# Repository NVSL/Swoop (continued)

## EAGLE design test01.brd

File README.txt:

Swoop is a library of Python objects for representing and manipulating
Cadsoft Eagle board, schematic, and library files used in designing printed
circuit boards (PCBs).  It parses an input Eagle file, creates a internal
representation data structure that represents the file's contents,
provides accessors and mutators to query, read, and modify those contents, and
generates valid Eagle files as output.

Swoop was created by the NVSL (http://nvsl.ucsd.edu/) UCSD
(http://www.ucsd.edu/) as part of the Gadgetron project
(http://nvsl.ucsd.edu/index.php?path=projects/gadget)

Documentation is available here: http://nvsl.ucsd.edu/Swoop

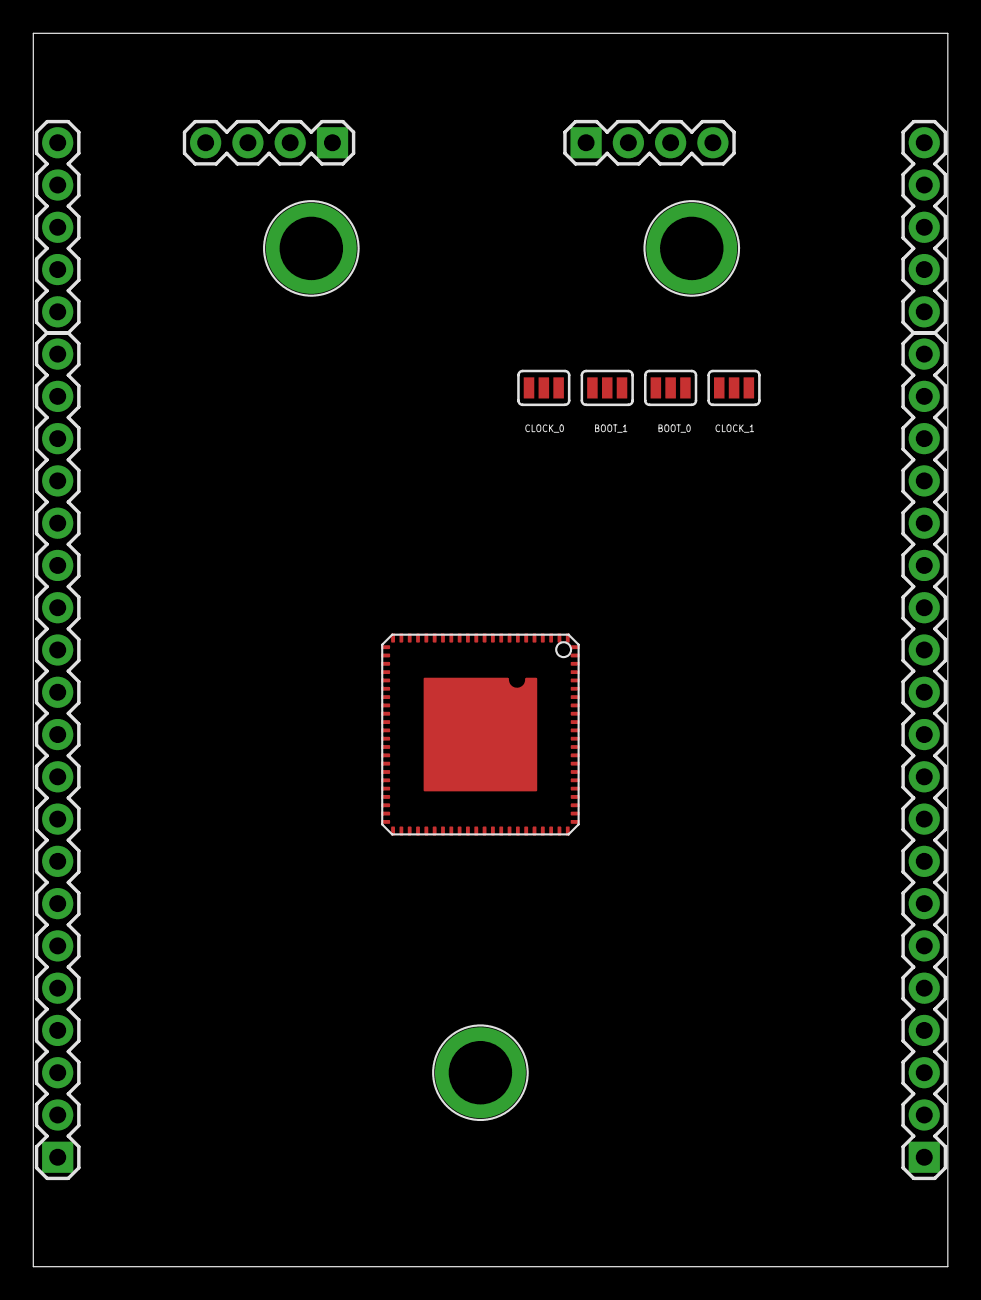
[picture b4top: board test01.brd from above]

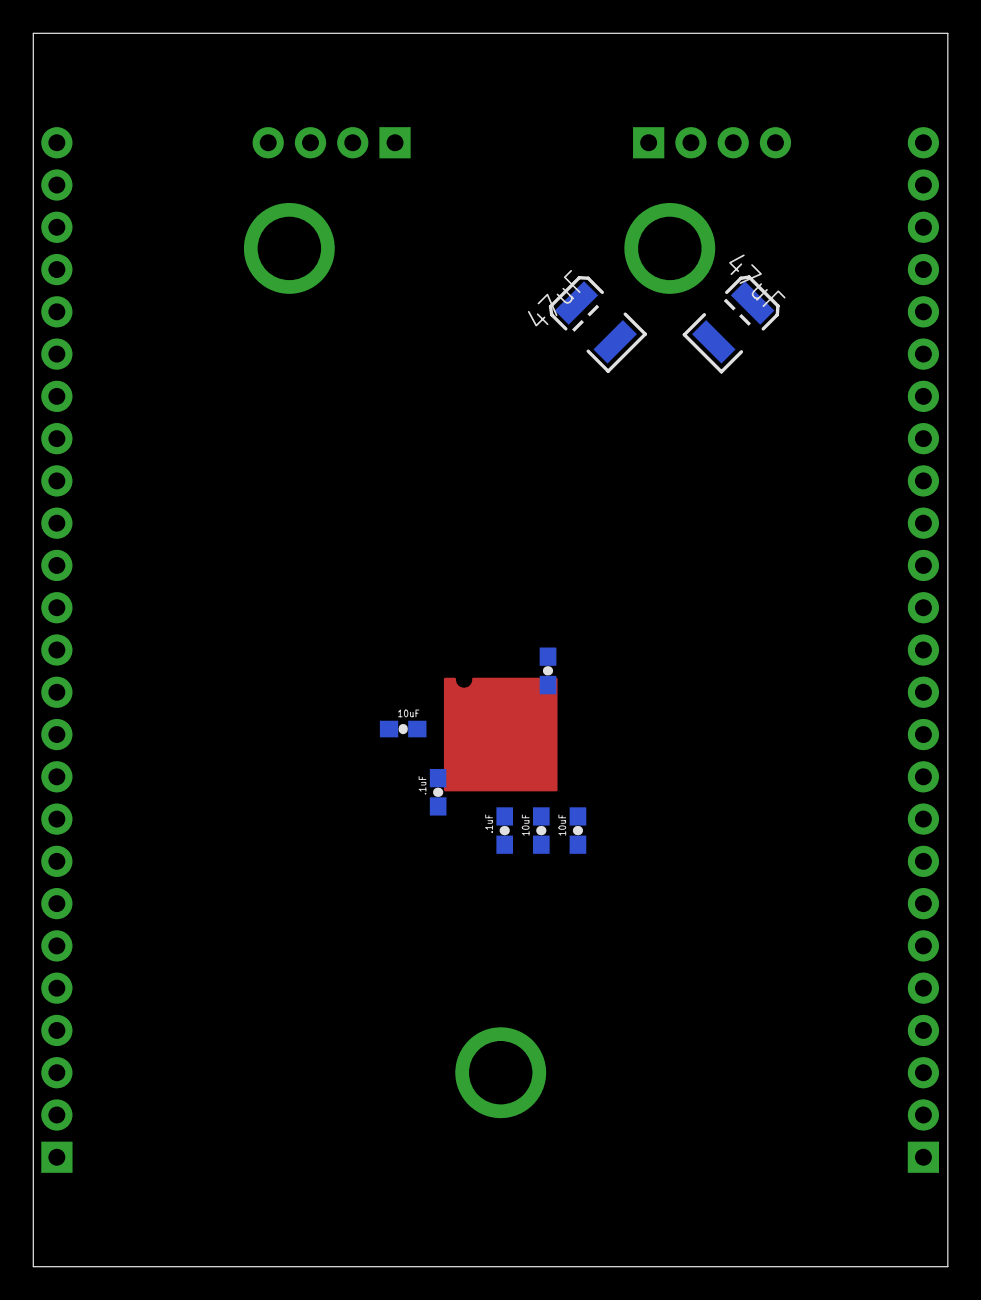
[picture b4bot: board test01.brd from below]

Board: 2 copper layers, 55.0 x 74.1 mm, 22 parts (8 on the bottom side), 57 nets, no tracks yet.

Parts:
1.25V, 3.3V: BANANA_CONN
BOOT_0, BOOT_1: SJ_3
C1, C2, C5: 10uF; 0603-CAP
C3, C4, C6: .1uF; 0603-CAP
C7, C8: 47uF; EIA3528
CLOCK_0: SJ_3
CLOCK_1: aoeu; SJ_3
J3: BANANA_CONN
JP2, JP4: M20; 1X20
JP3, JP7: 1X05
JP5, JP6: 1X04
U$1: ADSP-21479; QFN-88

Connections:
BOOT_CFG0: BOOT_0.2, U$1.2
BOOT_CFG1: BOOT_1.2, U$1.5
CLKIN: JP3.5, U$1.9
CLK_CFG0: CLOCK_0.2, U$1.7
CLK_CFG1: CLOCK_1.2, U$1.1
DAI_P01: JP2.9, U$1.37
DAI_P02: JP2.8, U$1.38
DAI_P03: JP2.13, U$1.31
DAI_P04: JP2.1, U$1.51
DAI_P05: JP2.6, U$1.43
DAI_P06: JP2.7, U$1.42
DAI_P07: JP2.11, U$1.35
DAI_P08: JP2.2, U$1.50
DAI_P09: JP2.5, U$1.44
DAI_P10: JP2.4, U$1.45
DAI_P11: JP4.7, U$1.58
DAI_P12: JP4.6, U$1.57
DAI_P13: JP2.12, U$1.34
DAI_P14: JP4.1, U$1.52
DAI_P15: JP4.5, U$1.56
DAI_P16: JP4.4, U$1.55
DAI_P17: JP4.3, U$1.54
DAI_P18: JP4.2, U$1.53
DAI_P19: JP2.10, U$1.36
DAI_P20: JP2.3, U$1.48
DPI_P01: JP3.2, U$1.16
DPI_P02: JP3.1, U$1.17
DPI_P03: JP7.5, U$1.18
DPI_P04: JP7.3, U$1.21
DPI_P05: JP7.4, U$1.20
DPI_P06: JP7.2, U$1.22
DPI_P07: JP2.20, U$1.25
DPI_P08: JP7.1, U$1.24
DPI_P09: JP2.19, U$1.26
DPI_P10: JP2.18, U$1.27
DPI_P11: JP2.17, U$1.28
DPI_P12: JP2.16, U$1.29
DPI_P13: JP2.15, U$1.30
DPI_P14: JP2.14, U$1.32
FLAG0: JP4.10, U$1.68
FLAG1: JP4.11, U$1.70
FLAG2: JP4.12, U$1.71
FLAG3: JP4.13, U$1.72
GND: BOOT_0.1, BOOT_1.1, C1.1, C2.1, C3.1, C4.1, C5.1, C6.1, C7.C, C8.C, CLOCK_0.1, CLOCK_1.1, J3.P$1, U$1.6, U$1.60, U$1.73, U$1.74, U$1.76, U$1.PAD
TCK: JP4.18, U$1.84
TDI: JP4.17, U$1.83
TDO: JP4.16, U$1.80
THD_B51AD: JP4.9, U$1.62
THD_M: JP4.8, U$1.61
TMS: JP4.20, U$1.87
VDD_EXT+THD: 3.3V.P$1, BOOT_0.3, BOOT_1.3, C1.2, C2.2, C3.2, C4.2, C7.A, CLOCK_0.3, CLOCK_1.3, JP5.1, JP5.2, JP5.3, JP5.4, U$1.3, U$1.11, U$1.23, U$1.40, U$1.47, U$1.63, U$1.75, U$1.81
VDD_INT: 1.25V.P$1, C5.2, C6.2, C8.A, JP6.1, JP6.2, JP6.3, JP6.4, U$1.4, U$1.8, U$1.12, U$1.13, U$1.15, U$1.19, U$1.33, U$1.39, U$1.41, U$1.46, U$1.49, U$1.59, U$1.64, U$1.65, U$1.66, U$1.67, U$1.69, U$1.77, U$1.82, U$1.85, U$1.88
XTAL: JP3.4, U$1.10
~EMU: JP4.15, U$1.79
~RESET: JP4.19, U$1.86
~RESETOUT/~RUNRSTIN: JP3.3, U$1.14
~TRST: JP4.14, U$1.78

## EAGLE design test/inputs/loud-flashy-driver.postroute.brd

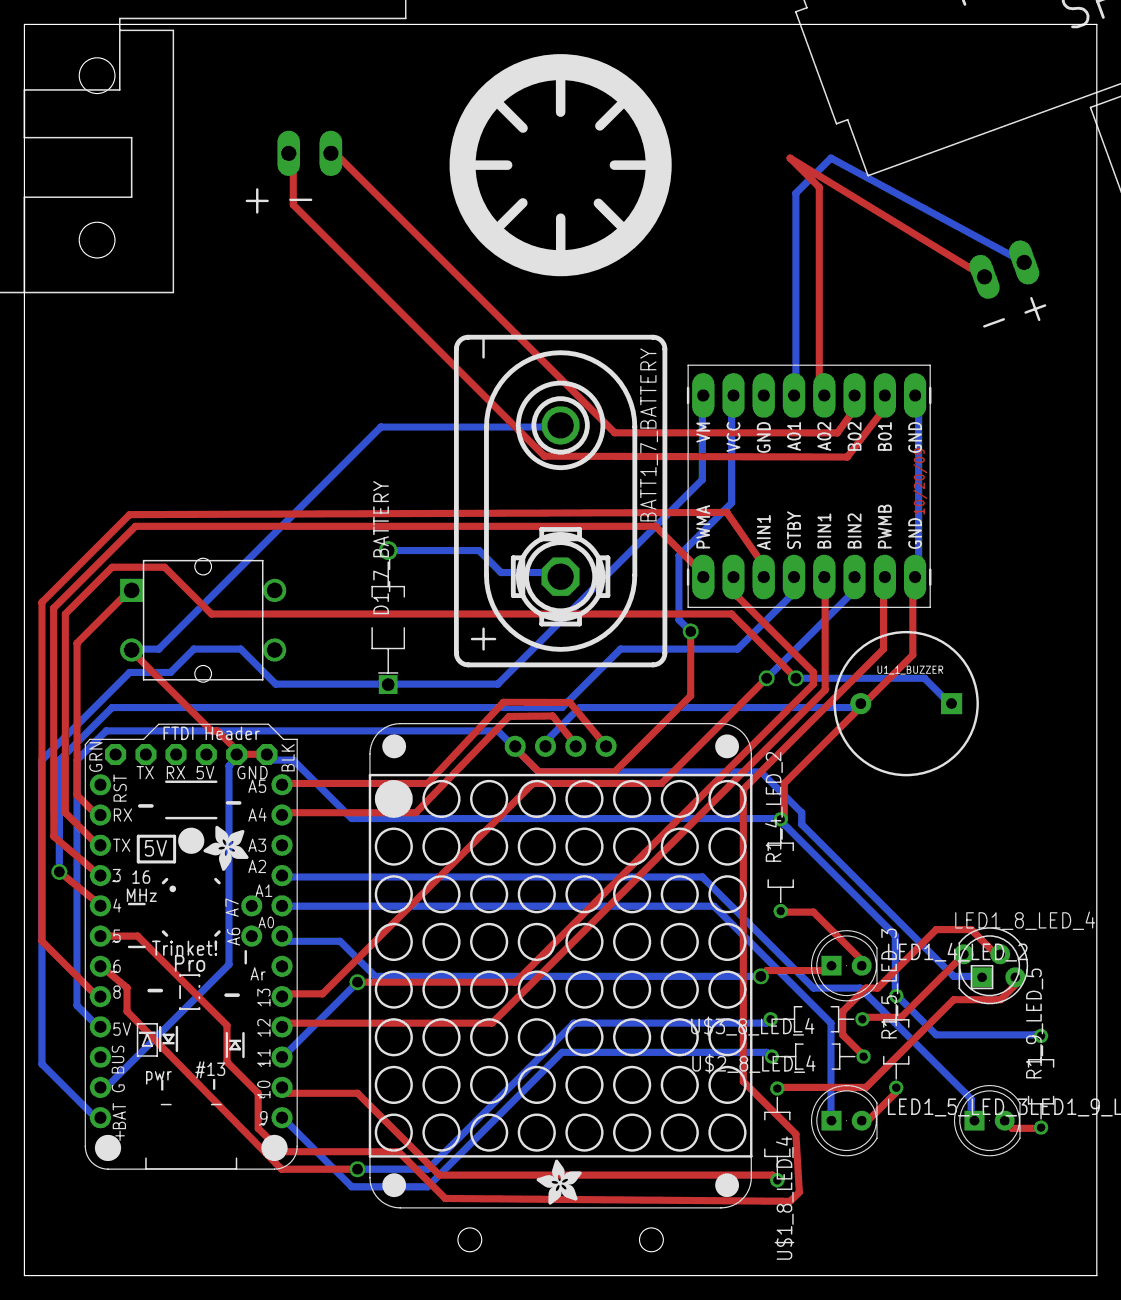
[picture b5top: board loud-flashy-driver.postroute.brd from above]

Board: 2 copper layers, 90.0 x 105.0 mm, 21 parts (0 on the bottom side), 31 nets.

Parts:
B1_0_BUTTON: BUTTON-TACTILE-SQUARE; BUTTON-TACTILE-SQUARE-ADAFRUIT1010
BATT1_7_BATTERY: BATTERY-9V-VERTICAL; BATTERY_9V_KEYSTONE_968
D1_7_BATTERY: DIOAD1125W78L520D270_HS
DRVR_2_DRIVE: SPARKFUN_DUAL_MOTOR_DRIVER-BOB; SPARKFUN_DUAL_MOTOR_DRIVER
LED1_4_LED_2, LED1_5_LED_3, LED1_9_LED_5: LED5MM
LED1_8_LED_4: RGBLED_CA-5MM; LED5MMRGB
L_2_DRIVE: SOLARBOTICS_GM2_LEFTSPARKFUN_HOBBY; SPARKFUN_HOBBY_MOTOR_LEFT
R1_4_LED_2, R1_5_LED_3, R1_9_LED_5: 330; RESAD770W45L370D210_HS
R_2_DRIVE: SOLARBOTICS_GM2SPARKFUN_HOBBY; SPARKFUN_HOBBY_MOTOR
U1_1_BUZZER: BUZZER-12MM
U1_3_DISPLAY_2: ADAFRUIT-1.2IN-8X8-LED-BACKPACK
U1_6_CASTER: ADAFRUIT-3/4IN-CASTER
U1_10_BRAIN: ADAFRUIT-PRO-TRINKET-5V
U1_11_PENHOLDER: PENHOLDER
U$1_8_LED_4, U$2_8_LED_4: 100; RESAD770W45L370D210_HS
U$3_8_LED_4: 150; RESAD770W45L370D210_HS

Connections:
+5V_10_BRAIN: DRVR_2_DRIVE.VCC, LED1_8_LED_4.2, U1_3_DISPLAY_2.VDD, U1_10_BRAIN.+5V
A0_10_BRAIN: LED1_4_LED_2.A, U1_10_BRAIN.A0
A01_2_DRIVE: DRVR_2_DRIVE.A01, R_2_DRIVE.+
A1_10_BRAIN: LED1_5_LED_3.A, U1_10_BRAIN.A1
A02_2_DRIVE: DRVR_2_DRIVE.A02, R_2_DRIVE.-
A2_10_BRAIN: LED1_9_LED_5.A, U1_10_BRAIN.A2
A4_10_BRAIN: U1_3_DISPLAY_2.SDA, U1_10_BRAIN.A4
A5_10_BRAIN: U1_3_DISPLAY_2.SCL, U1_10_BRAIN.A5
B01_2_DRIVE: DRVR_2_DRIVE.B01, L_2_DRIVE.+
B02_2_DRIVE: DRVR_2_DRIVE.B02, L_2_DRIVE.-
D3_10_BRAIN: DRVR_2_DRIVE.PWMA, U1_10_BRAIN.D3
D4_10_BRAIN: DRVR_2_DRIVE.STBY, U1_10_BRAIN.D4
D5_10_BRAIN: DRVR_2_DRIVE.PWMB, U1_10_BRAIN.D5
D6_10_BRAIN: U1_10_BRAIN.D6, U$3_8_LED_4.2
D8_10_BRAIN: DRVR_2_DRIVE.AIN1, U1_10_BRAIN.D8
D9_10_BRAIN: U1_10_BRAIN.D9, U$2_8_LED_4.2
D10_10_BRAIN: U1_10_BRAIN.D10, U$1_8_LED_4.2
D11_10_BRAIN: DRVR_2_DRIVE.AIN2, U1_10_BRAIN.D11
D12_10_BRAIN: DRVR_2_DRIVE.BIN1, U1_10_BRAIN.D12
D13_10_BRAIN: DRVR_2_DRIVE.BIN2, U1_10_BRAIN.D13
GND_0_BUTTON: B1_0_BUTTON.S, BATT1_7_BATTERY.N, DRVR_2_DRIVE.GND, DRVR_2_DRIVE.GND2, R1_4_LED_2.2, R1_5_LED_3.2, R1_9_LED_5.2, U1_1_BUZZER.-, U1_3_DISPLAY_2.GND, U1_10_BRAIN.GND, U1_10_BRAIN.GND1, U1_10_BRAIN.GND2
unnamed: LED1_4_LED_2.K, R1_4_LED_2.1
unnamed: LED1_5_LED_3.K, R1_5_LED_3.1
unnamed: BATT1_7_BATTERY.P, D1_7_BATTERY.A
unnamed: LED1_8_LED_4.4, U$1_8_LED_4.1
unnamed: LED1_9_LED_5.K, R1_9_LED_5.1
unnamed: LED1_8_LED_4.3, U$2_8_LED_4.1
unnamed: LED1_8_LED_4.1, U$3_8_LED_4.1
RXD1_10_BRAIN: B1_0_BUTTON.P, U1_10_BRAIN.RXD1
TXD1_10_BRAIN: U1_1_BUZZER.+, U1_10_BRAIN.TXD1
VM_2_DRIVE: D1_7_BATTERY.C, DRVR_2_DRIVE.VM, U1_10_BRAIN.VBAT

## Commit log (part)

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2014-11-14 Example of circuits from code
2014-11-14 Framework for circuits from code
2014-11-17 Tester for HighEagle interface
2014-11-19 More circuits by code import implementation
2014-11-23 one more feature
2015-01-06 bug fixes for labels/segments
2015-01-21 reorged part resolution code
2015-01-22 Added .api.gspec
2015-01-24 Fixed some bugs in part resolution and improved error handling for parsing Digikey spreadsheets
2015-01-25 test for unit parsing
2015-01-28 missing code
2015-02-03 Fixed and re-enabled a test
2015-02-05 test fixes
2015-02-09 Better part parameter parsing
    Fixed curvature of wires
    Support for diodes
    Multiple part database support
    Standardized attributes
    fixed tests
    code for building GENERIC, RESOLVED, and UNRESOLVED devicesets automatically
2015-02-10 Resonator support. Better tests and Makefiles
2015-02-12 Cleanup, error checking, and pretty printing of values in resolved parts
2015-02-12 Get rid of nF
2015-02-16 Repair base.lbr
2015-02-18 Added EagleTools.py for useful functions that don't belong in HighEagle.py. Current tools are for cleaning up layers in eagle files.
    Added EagleFilePartVisitor base class for building visitors.
    Made sure layers are in sorted order.
    Updated NVSLLayers.lbr to match Eagle manual + gadgetron layers
    Picker.py now fixes up layers automatically.
    Picker.py now takes resolver library and layers library
    Cleaner tests
2015-02-22 Part picker cleanup.
    Added environment variable support to GadgetronConfig
    Made picker use GadgetronConfig
    Added picker configuration variables to gadgetron config
    Move picker libraries into Libraries/ hierarchy.
    Moved standard layer lib into Libraries/Parts/Eagle
    Added CircuitsByCode to PATH in setup.
2015-02-23 Moved picker tool to its directory. Renamed koala
2015-02-24 Added support for new leaf tags that appear in brd files.
    Started using logging module for logging. We should use it more: import logging as log
    New command line options for Koloa to make it easier to diagnose unresolved components. You can specify parts to resolve and ask for verbose mode.
    Added a kludge to work around problems rendering some values when printing out resolved parts in Koala
    New --force option for fixEagle to forcibly install layers.
2015-03-01 Complete rework of HighEagle.py.
    Instead of being written by hand, it's autogenerated from HighEagle.jinja.py.
    A couple of tools, most notably GenerateHigHeagle.py use Jinja and the
    eagle DTD to autogenerate classes for eagle files.
    Look at GenerateHigHeagle.py for comments describing how it works.
    This change adds some complexity. GenerateHighEagle.py is not so easy
    to edit and you need to know the basics of the jinja templating
2015-03-01 bug fixes
2015-03-02 Documentation. See the top of GenerateHighEagle.py
2015-03-02 Small bug fix for _EXTERNAL_ devices
2015-03-03 Lots of documentation. Code cleanup. Got rid perl-generated intermeidate attribute file. Fix for lists of attributes in <element>. Some test boards and schematics.
2015-03-03 Better type information for parsing and documentation.
2015-03-05 Removed arguments from all constructors to make extending classes easier.
2015-03-05 Typeo
2015-03-08 The libraries are in place for Koala, thanks mostly to Stephen Deiss.
    Generating the CSV file for the parts database is very error-prone.
2015-03-09 Added koala to the gadget making tool chain.
    Update 3mm, 5mm, and 10mm LEDs to use koala for their resistors. It's a start.
    Fix to make jettest build again.
    modified gadgetmaker2 to use HighEagle for file output (and to normalize the layers on the .brd and .sch files it generates)
    Docs for EagleTools.py
    Added function to EagleTools.py to propagate parts from .sch to .brd files.
    Added function to EagleTools.py rebuild signals in brd based on sch.
2015-03-11 missing file
2015-03-11 Doc cleanup for name change
2015-03-12 asciitree for library generation. Moved tests for Koala and Swoop to python unittest.
2015-03-14 build fixes
2015-03-14 Made the Swoop interface slightly more fluent by changing filter_* to with_*
2015-03-17 A probably-to-complex mechanism for extending Swoop.
2015-04-03 buildPackageSVGs should center the artwork inside the SVG bounding box.
2015-04-06 Accounting for polygon and wire widths in get_bounding_rectangle.
2015-04-08 Swoop extensions folder
2015-04-09 made 'width' on <dimension> tags optional because eagle omit it sometimes
2015-04-15 Improved bounding boxes, with tests. Doesn’t work with all types of pads yet. Also supports querying board elements now
2015-04-17 Major improvements to bounding boxes. Now supports: arcs (with width), long pads, offset pads, rotated offset/long pads, rotated octagons. With tests.
2015-04-27 Monkey patch chaos: experimented with just normal monkey patching instead of Mixin and repeatedly doing isinstance(). Not sure which is worse.
2015-05-01 Example for on-top-of-Swoop layer use
2015-05-04 Tying up loose ends in Swoop. Clean up docs.
2015-05-04 disable tests if we don't have Rectangle
2015-05-04 bug fix"
2015-05-05 More work towards distribution
2015-05-05 reorg for distribution
2015-05-06 yet still more prep for distribution
2015-05-08 Complete reorganization to match setuptool standard practice.
    Setuptools is really pretty awesome. Especially 'develop' mode
    Also, if you
    export USE_VENV=yes
    Everything gadgetron related will get its own python directory (in Gadgets/Python/). This will also let you use develop mode.
2015-05-08 Significantly cleaned up the monkey patch chaos. Rather than use isinstance() or monkey patching, I tried to take advantage of duck typing and hasattr().
    Mirroring each individual child element of a package in SwoopGeom should now look exactly the same as if you mirrored the whole package in Eagle.
2015-05-08 Bad indexing
2015-05-08 doc fixes
2015-05-15 -RGBLED had a bunch of stuff missing from the important layers -Did a library update on SF-dual-motor-driver because its package was wrong (I’m not using its package anyway but why not)
2015-05-15 Package bounding box
2015-05-30 Unused argument
2015-06-13 Panelize script
2015-06-17 broke out basic eagle code processor schematics into seperate class
2015-06-18 new quadcopter schematic
    Some type checking on arguments to Swoop functions.
    Swoop tool to snap schematic items to a grid
    Swoop documentation fixes.
    New Dual Motor component.
    Some more cap sizes.
    Koala bug fixes.
2015-06-29 better support for instances
2015-07-15 More gracefully handle missing layers
2015-07-16 tricky bug fix
2015-07-22 bug fix for singleton parent
2015-07-23 More comments
2015-07-26 use getters consistently
2015-07-27 Improved consistency for get_layers(). Added type checking for attribute setters. got rid of Attribute.in_library. Added support for dumping XML version of an EFP. Tests for Attribute.constant handli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
2015-08-03 Test for Swoop not opending Quadcopter.koala.sch
2015-08-04 Swoop opening and writing Trinket will cause bug, test added
2015-08-07 error handling
2015-09-13 Circular rubouts work
2015-09-24 Convert Eagle wire paths into laser turtle code.
2015-10-11 No CGAL unless we need it
2015-10-11 Add back in skipping tests
2015-10-13 Wrote test for overlap checking, fixed things
2015-10-14 It did not like that import
2015-10-28 Forgot file
2015-11-09 irrelevant change
2015-11-19 Add support for Eagle 7.4 and 7.5
2015-12-23 Use CGAL segments for wires with width == 0 as well wires without a width
2015-12-24 Support for module-based mixins
2015-12-26 Improved layer lookup and layer mirroring
2015-12-27 First parts of a Shapely-based geometry extension. It's cleaner than the CGAL-based one system. Still much to do.
2015-12-31 Renamed Shapely to ShapelySwoop
2015-12-31 Improved tests
2015-12-31 Tool renumber layers
2015-12-31 renumbered layers
2016-01-07 Produce smaller svgs
2016-02-17 Support for parsing DRU files
2016-02-18 Docs for DRU file in open((
2016-02-20 .gitignore
2016-02-24 Nicer errors when parsing problems occur
2016-02-25 Mirroring fixes
2016-02-28 Don't open the file until writing it assured
2016-03-02 Better parsing error reporting. Move element transforms to static methods. New and improved utilities for board building
2016-03-08 handle curves properly
2016-03-08 add library cache to docs
2016-03-09 Support for text.
2016-03-09 Tests for text geometry handling
2016-03-10 add ' '
2016-03-29 utility to create new library from orphaned devices in a schematic.
2016-03-29 Utility function for gathering attribute values
2016-04-13 normalized reference designators. Part renaming. Docs
2016-05-07 documentation improvements. Handle default font properly
2016-06-14 Small tweaks
2016-06-14 Commit before release 0.4.0
2016-06-22 return renaming information after normalizing refdes
2016-07-03 Support for loading from a stream
2016-07-16 Remove test that doesn't pass consistently
2016-07-23 Commit before release 0.4.1
2016-07-24 progress toward successful deployment
2016-08-10 fix build target. Cleanup
2016-08-11 fix build probems
2016-08-15 Configure entry_points in setup.py
2016-08-18 use a version of lxml that builds on mac
2016-09-03 allow for filled circles in shapely swoop
2016-10-24 Handle locked attributes correctly. Resolves #5
2017-05-24 make 'without' work
2017-07-10 ignore generated files
2017-07-10 make Swoop Py2k/3k compatible
    Tested on:
    - Python 2.7.13
    - Python 3.6.1
    Passes all tests in both 2k and 3k except
    - FAIL: test_Mixin (test.test_Extension.TestExtension)
    - FAIL: test_Search (test.test_Swoop.TestSwoop)
2017-07-11 add Python3 to trove classifiers
2017-07-18 do not mark non-required library sections as required
    From the DTD:
    <!ELEMENT library (description?, packages?, symbols?, devicesets?)>
    None of these sections are requried, if they are empty, Swoop would generate
    `<symbols/>` (or whichever) tags inside `library`s which Eagle would then
    delete the next time it opened the file
    As an example of a library with no symbols or devicesets, we have a library
2017-09-22 Added checks for non-unique parents
2017-12-06 break dep on gtron
2017-12-06 Commit before release 0.5.3
2018-12-31 fix geometry regressions. Version-based dtds
2018-12-31 make element attributes a list
2018-12-31 script to diff files that swoop seems to have mangled
2018-12-31 handle unvalidating writing
2018-12-31 small debugging support
2019-01-01 a bunch of fixes to code and test inputs to get the tests to past. I believe several of test inputs were malformed because they were generated by buggy versions of swoop
2019-01-24 correctly use pkg_resources to access package files
2019-02-19 Commit before release 0.6.0
2019-03-09 more eagle versions
2019-03-19 fix parsing of some stop, thermals, and cream for smds and 'constant' on attributes
2019-04-12 Reorg, fix release, some bug fixes.
2019-04-12 Fix deployment
2019-04-12 Commit before release 0.6.4
2019-04-14 fix requirements
2019-04-14 re-add generate swoop
2019-04-14 use latest lxml
2019-04-14 fix conflict
2019-04-14 test dependences
2019-04-14 make tests work with travis (and pass)
2019-04-17 tests for deployed code
2019-11-20 Correct the following 2 error message, when the default.dru ist used:
    Error message 1:
    File "d:/swoop-06.5/test_library_technologies.py", line 49, in add_lbr
    lbrf = Swoop.EagleFile.from_file(file)
    File "c:\program files\python37\lib\site-packages\swoop-0.6.5-py3.7.egg\Swoop\Swoop.py", line 1224, in from_file
    n = cls.from_stream(cls.get_library_file_type(), f, bestEffort, DRUFile, pickle, filename=filename)
    File "c:\program files\python37\lib\site-packages\swoop-0.6.5-py3.7.egg\Swoop\Swoop.py", line 1184, in from_stream
2020-07-02 Decode unicode before regex parsing
    The XML library requires bytes rather than strings, so leave the file
    opening as binary. However, the regex needs a string to operate on, so
    let's fix that.
    Fixes #15.
2020-09-09 cleanup error handling logic
2020-09-11 fix a bunch of bugs with various versions of the dtd.
